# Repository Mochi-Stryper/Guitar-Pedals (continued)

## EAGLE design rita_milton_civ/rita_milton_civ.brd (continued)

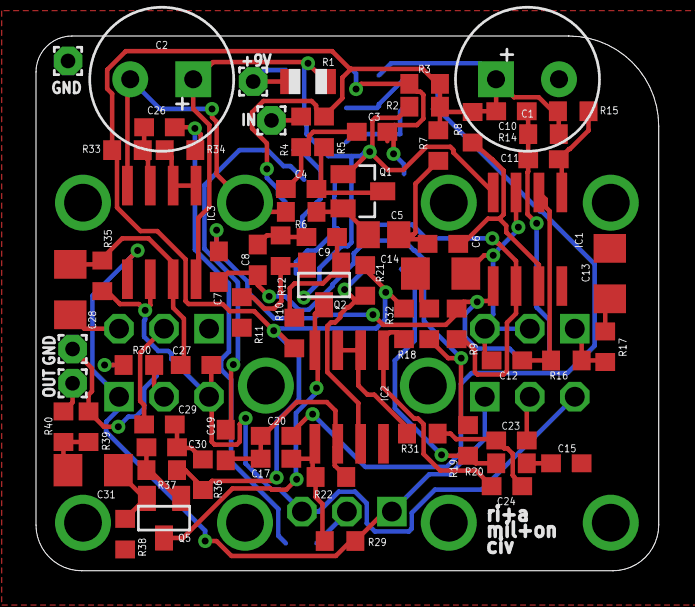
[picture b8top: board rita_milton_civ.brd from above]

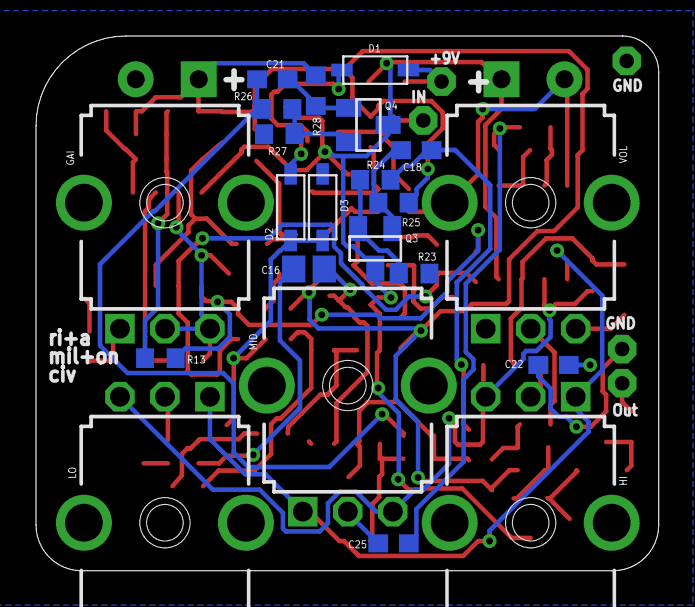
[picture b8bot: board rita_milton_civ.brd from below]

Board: 2 copper layers, 34.6 x 29.7 mm, 92 parts (22 on the bottom side), 54 nets.
